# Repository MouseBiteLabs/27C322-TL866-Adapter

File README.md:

# 27C322/160/800/400 Programming Adapter for the TL866 and T48

This adapter allows you to program the 27C322, 27C160, 27C800, and 27C400 chips on your MiniPro TL866 programmer. The 27C322/160/800 EPROMs are 42 pins wide, but the TL866 and TL866II programmer only has a 40-pin socket. If you choose the 27C4096 EPROM (4 Mbit) on the IC selection list, you can then use the on-board switches to manually switch upper address pins A18 to A20. This allows you to fill up a larger chip (27C322 has a storage space of 32 Mbit) in 4 Mbit chunks.

YES, these work with the T48 as well!

# Bill of Materials

Resistor wattage can be 1/10 W or larger.

| Reference Designator  | Part Number/Value | Footprint  |
| ------------- | ------------- | ------------- |
| R18  | 10 kΩ | 0805  |
| R19  | 10 kΩ | 0805  |
| R20  | 10 kΩ | 0805  |
| RE  | 10 kΩ | 0805  |
| RB  | 330 Ω | 0805  |
| Q1  | 2N3906 | SOT-23  |
| S18-S20  | <a href="https://www.digikey.com/short/tp5cw74d">DIP Switch x3, SPST</a> | --  |
| S1  | <a href="https://www.digikey.com/short/2q237b7r">Slide Switch, DPDT</a> | --  |
| xx  | <a href="https://www.ebay.com/sch/i.html?_from=R40&_trksid=p2380057.m570.l1313&_nkw=dip+42+socket&_sacat=0">Wide 42-pin DIP Socket</a> | DIP-42  |
| xx  | <a href="https://www.ebay.com/sch/i.html?_from=R40&_trksid=p2334524.m570.l1313&_nkw=40-pin+male+header+0.1%22&_sacat=0&LH_TitleDesc=0&_odkw=0.1%22+header+pins&_osacat=0">Male Header Pins</a> | 2x rows of 18-pin  |

# How to Use the Adapter

Load up the 27C4096 chip on the TL866 software, and load up the first chunk from your original file. Change the VPP to 12.5 V, as this is dictated for programming voltage in the datasheet. Then, uncheck the “Check ID” option. Note that if you have the new TL866II and are using “Xgpro” software, you need to uncheck “Pin Detect” as well. Your window should look like this:

Here’s a table of how data is programmed into the EPROM. If A18, A19, or A20 is a “0”, that means tie it to GND, or if you’re using the adapter, put the switch in the “OFF” position. If it’s a “1”, that means tie it to VCC, or if you’re using the adapter, put the switch in the “ON” position. Program the 4 Mbit chunks in sequential order in the banks.

For the 27C322, put the small DPDT switch in 27C322 mode (to the left) and use these DIP switch positions:

For the 27C160, put the small DPDT switch in non-27C322 mode (to the right) and use these DIP switch positions:

For the 27C800, put the small DPDT switch in non-27C322 mode (to the right) and use these DIP switch positions:

For the 27C400, put the small DPDT switch in non-27C322 mode (to the right) and keep all DIP switch positions OFF. Also, because the 27C400 is only 40 pins, and not 42 pins, make sure to put the EPROM with pins 1 and 42 exposed.

If you get an error while programming with the MiniPro – make sure your chips are in the correct orientation, each bank is blank, you’ve unchecked the “Check ID” box, and that you’ve selected a 27C4096 EPROM from the Select IC list. Also, make sure you’ve got the DPDT switch on the adapter board on the correct option.

# How the Adapter Works

Here’s a breakdown of the pinouts on the 27C322, 27C160, and the 27C4096.

Remember, the 27C4096 is the chip we’re going to tell the TL866 we’re programming. The X’s signify an address pin that goes unused on that chip. We’ll be adding three switches to manually control these pins – A18, A19, and A20. You’ll note that the 322 and 160 share every single pin, except that 160’s don’t utilize A20, and the VPP and /OE pins are a bit different.

According to the datasheet for the 27C322, pin 13 (or /GVpp as it’s defined) combines the /OE (output enable) pin and the VPP (programming voltage) pins into one. The 4096, however, keeps these pins separate. This isn’t too much of a problem, though, if we take a look at the operating modes of the 322 we can see that we never really need the /GVpp pin to be anything but zero volts or the programming voltage.

Here, VIL notates logic low, or zero volts. VIH is logic high, or anywhere between 2 and VCC + 1 volts (according to the datasheet). You’ll notice that the only mode that uses VIH is “Output Disable” which isn’t really used while programming the EPROM. So we only really need to switch pin 13 between ground and VPP (which means we can ignore pin 20 on the TL866 completely for programming the 27C322). Unfortunately, the TL866 switches VPP between the programming voltage and VCC voltage, so we need to add a bit of circuitry to change that VCC to GND.

The PNP transistor above conducts when the emitter voltage is greater than the base voltage. During programming, the VPP pin from the TL866 applies the high programming voltage. When this happens, current flows through the base resistor (RB), and pulls pin 13 on the 27C322 to VPP. Then, when the VPP pin on the programmer drops to VCC voltage, the base current drops and the transistor stops conducting. This causes pin 13 to be pulled to VSS through the collector resistor (RC).

Now, taking care of the extra address pins is just using simple switches with pull-down resistors.

With this extra circuitry, we can make a standalone 27C322 adapter for the TL866. However, if you check that table again up at the top, you should’ve noticed that the 27C322 and 27C160 (and by extension, the 27C800 and 27C400) share a lot of common pins. The only real difference is which pin is used for the programming voltage – pin 32 on the 160 is the VPP pin, but on the 322 this is the A20 pin. We can easily reroute this using a double-pole-double-throw (DPDT) switch.

So with the extra circuitry, we now have our finished product, capable of allowing the TL866 to program 27C322s, 160s, 800s, and 400s.

# License

Licensed under the TAPR Open Hardware License (www.tapr.org/OHL)

©MouseBiteLabs 2022

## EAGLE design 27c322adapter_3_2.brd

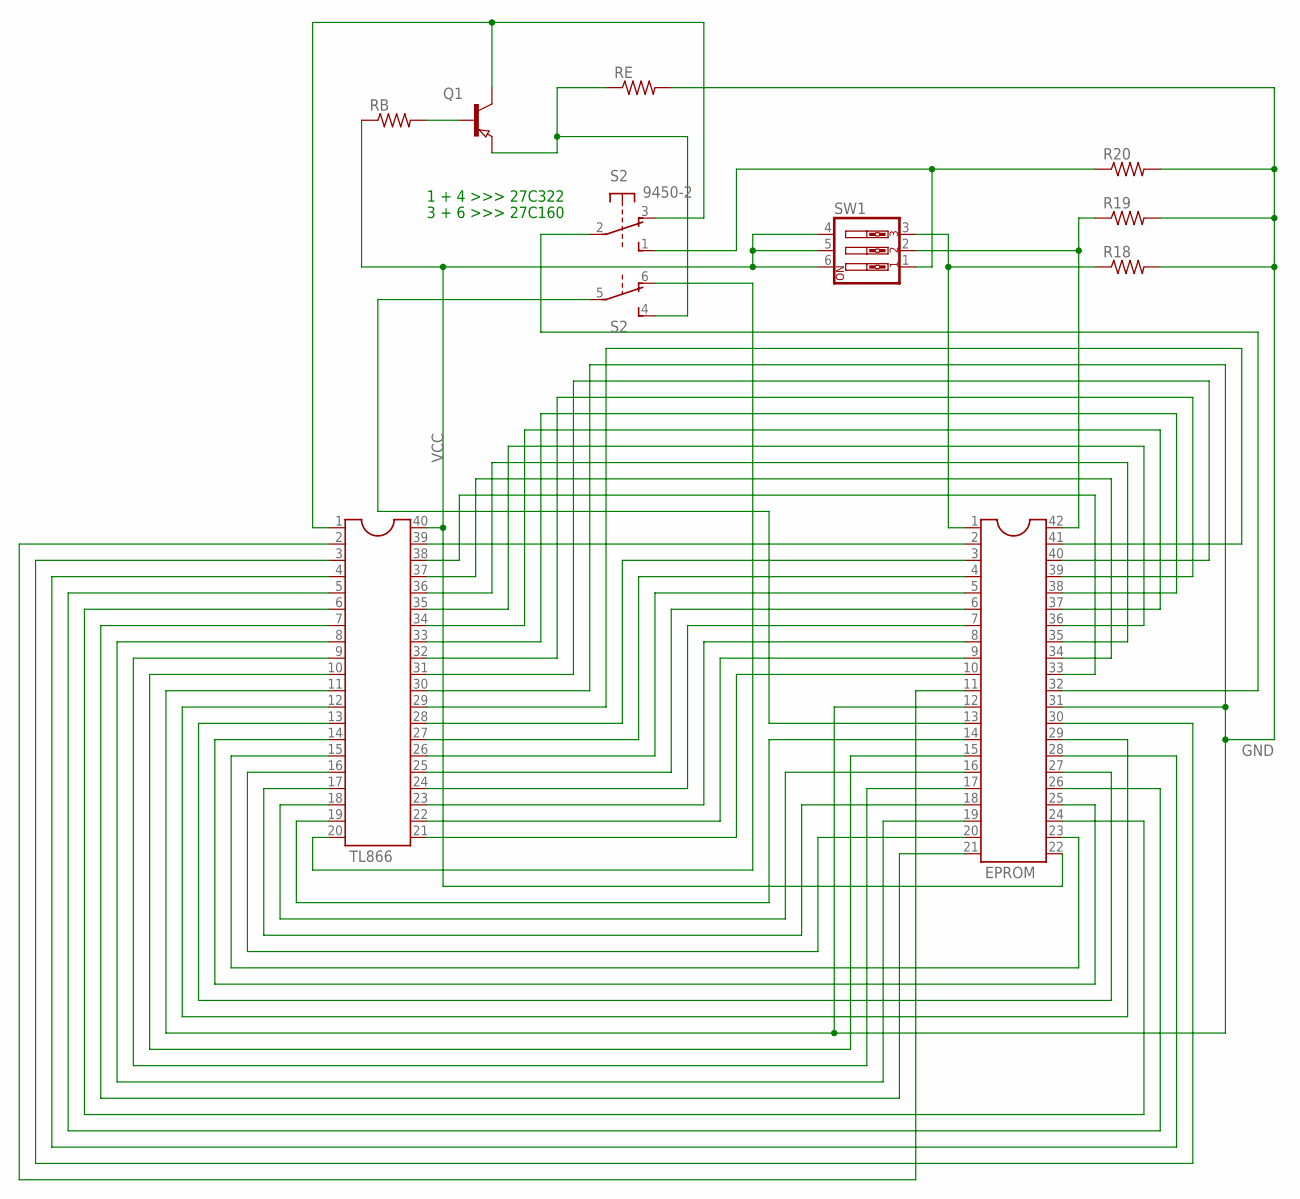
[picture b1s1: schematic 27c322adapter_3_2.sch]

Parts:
IC1: EPROM; DIL42_SLIM
Q1: PNP-TRANSISTOR_SOT23; SOT23
R18, R19, R20: R-US_R0805; R0805
RB: R-US_R0805; R0805
RE: R-US_R0805; R0805
S2: 9450-2
SW1: SW_DIP-3; EDG-03
TL866: TL866; DIL40_SLIM

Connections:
GND: IC1.12, IC1.31, R18.2, R19.2, R20.2, RE.2, TL866.11, TL866.30
unnamed: IC1.32, S2.2
unnamed: IC1.2, TL866.39
unnamed: IC1.33, TL866.38
unnamed: IC1.34, TL866.37
unnamed: IC1.35, TL866.36
unnamed: IC1.36, TL866.35
unnamed: IC1.37, TL866.34
unnamed: IC1.38, TL866.33
unnamed: IC1.39, TL866.32
unnamed: IC1.40, TL866.31
unnamed: IC1.42, R19.1, SW1.2
unnamed: IC1.41, TL866.29
unnamed: IC1.3, TL866.28
unnamed: IC1.4, TL866.27
unnamed: IC1.5, TL866.26
unnamed: IC1.6, TL866.25
unnamed: IC1.7, TL866.24
unnamed: IC1.8, TL866.23
unnamed: IC1.9, TL866.22
unnamed: IC1.10, TL866.21
unnamed: S2.6 (O), TL866.20
unnamed: IC1.14, TL866.19
unnamed: IC1.16, TL866.18
unnamed: IC1.18, TL866.17
unnamed: IC1.20, TL866.16
unnamed: IC1.23, TL866.15
unnamed: IC1.25, TL866.14
unnamed: IC1.27, TL866.13
unnamed: IC1.29, TL866.12
unnamed: Q1.1 (B), RB.2
unnamed: IC1.15, TL866.10
unnamed: IC1.17, TL866.9
unnamed: IC1.19, TL866.8
unnamed: IC1.21, TL866.7
unnamed: IC1.24, TL866.6
unnamed: IC1.26, TL866.5
unnamed: IC1.28, TL866.4
unnamed: IC1.30, TL866.3
unnamed: IC1.11, TL866.2
unnamed: Q1.3 (C), S2.3 (O), TL866.1
unnamed: IC1.1, R18.1, SW1.3
unnamed: IC1.13, S2.5
unnamed: R20.1, S2.1 (S), SW1.1
unnamed: Q1.2 (E), RE.1, S2.4 (S)
VCC: IC1.22, RB.1, SW1.4, SW1.5, SW1.6, TL866.40

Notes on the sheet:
1 + 4 >>> 27C322
3 + 6 >>> 27C160

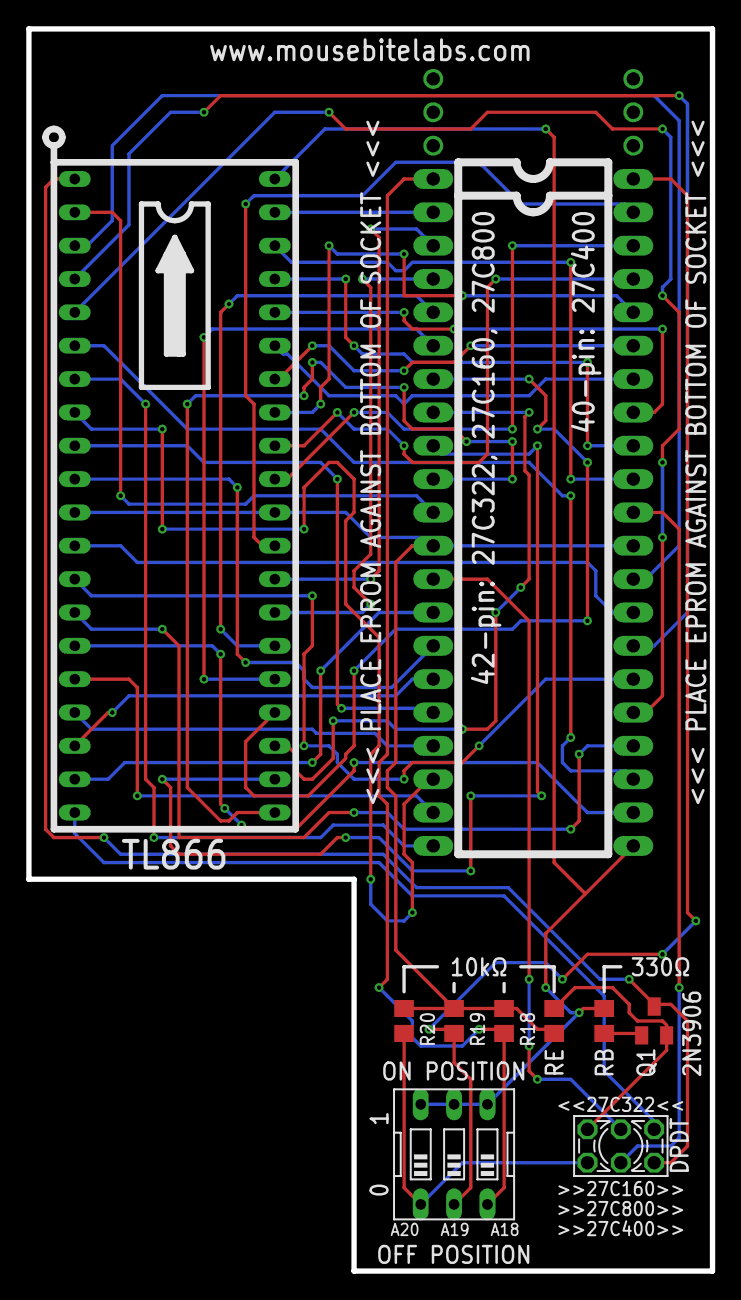
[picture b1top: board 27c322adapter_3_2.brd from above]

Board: 2 copper layers, 52.1 x 94.6 mm, 10 parts (0 on the bottom side), 46 nets.

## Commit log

2022-06-02 Create LICENSE
